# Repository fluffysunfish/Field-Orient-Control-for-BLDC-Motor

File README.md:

# Field-Orient-Control-for-BLDC-Motor

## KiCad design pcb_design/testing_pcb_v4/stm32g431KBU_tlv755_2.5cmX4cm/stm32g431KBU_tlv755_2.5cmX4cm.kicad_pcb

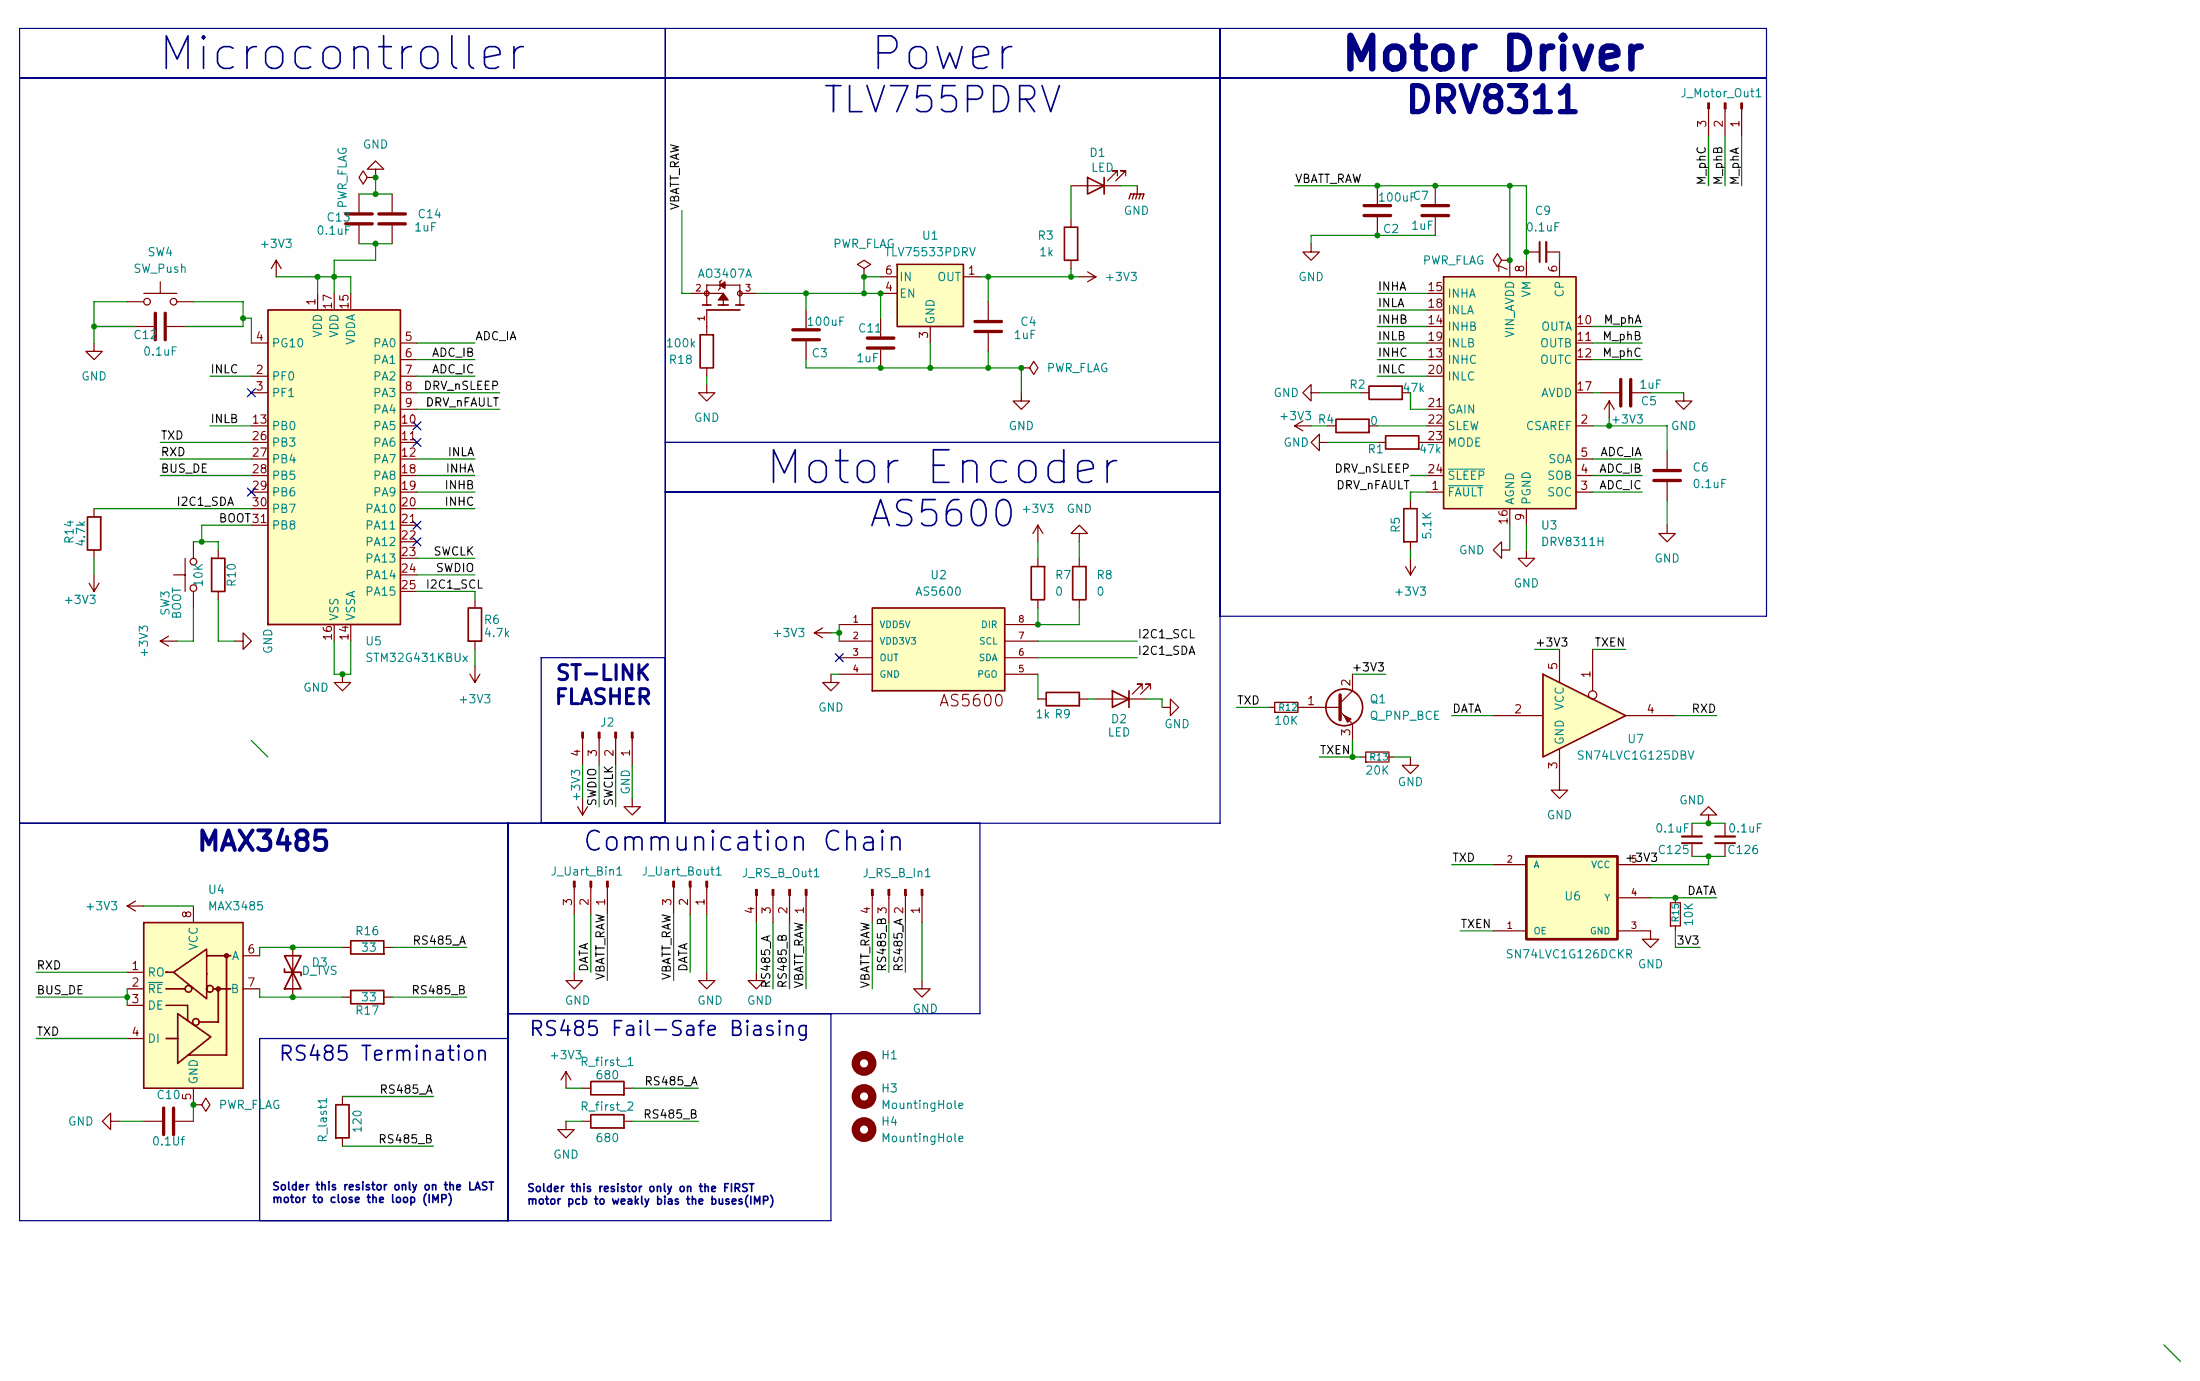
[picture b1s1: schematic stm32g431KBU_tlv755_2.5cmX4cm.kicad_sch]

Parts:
C2, C3: 100uF; C_0805_2012Metric
C4: 1uF; C_0805_2012Metric
C5: 1uF; C_0402_1005Metric
C6: 0.1uF; C_0402_1005Metric
C7, C11, C14: 1uF; C_0603_1608Metric
C9, C12, C13: 0.1uF; C_0603_1608Metric
C10: 0.1Uf; C_0402_1005Metric
C125, C126: 0.1uF; C_0603_1608Metric_Pad1.08x0.95mm_HandSolder
D1, D2: LED; LED_0603_1608Metric
D3: D_TVS; TSOT-23
H1, H3, H4: MountingHole; MountingHole_2.2mm_M2
J2: ST-LINK Flasher; PinHeader_1x04_P2.54mm_Vertical
J_Motor_Out1: Conn_01x03_Pin; PinHeader_1x03_P2.54mm_Vertical
J_RS_B_In1: Conn_01x04_Pin; JST_PH_S4B-PH-K_1x04_P2.00mm_Horizontal
J_RS_B_Out1: Conn_01x04_Pin; JST_PH_S4B-PH-K_1x04_P2.00mm_Horizontal
J_Uart_Bin1: Conn_01x03_Pin; JST_PH_S3B-PH-K_1x03_P2.00mm_Horizontal
J_Uart_Bout1: Conn_01x03_Pin; JST_PH_S3B-PH-K_1x03_P2.00mm_Horizontal
Q1: Q_PNP_BCE; SOT-23-3
Q2: AO3407A; SOT95P280X125-3N; PARTREV 5
R1, R2: 47k; R_0402_1005Metric
R3, R9: 1k; R_0402_1005Metric
R4: 0; R_0402_1005Metric
R5: 5.1K; R_0402_1005Metric
R6: 4.7k; R_0402_1005Metric
R7, R8: 0; R_0805_2012Metric
R10: 10K; R_0402_1005Metric
R12, R15: 10K; R_0603_1608Metric_Pad0.98x0.95mm_HandSolder
R13: 20K; R_0603_1608Metric_Pad0.98x0.95mm_HandSolder
R14: 4.7k; R_0805_2012Metric_Pad1.20x1.40mm_HandSolder
R16, R17: 33; R_0805_2012Metric
R18: 100k; R_0805_2012Metric
R_first_1, R_first_2: 680; R_0805_2012Metric_Pad1.20x1.40mm_HandSolder
R_last1: 120; R_0805_2012Metric_Pad1.20x1.40mm_HandSolder
SW3: BOOT; SW_Push_SPST_NO_Alps_SKRK
SW4: SW_Push; SW_Push_SPST_NO_Alps_SKRK
U1: TLV75533PDRV; WSON-6-1EP_2x2mm_P0.65mm_EP1x1.6mm
U2: AS5600; SOIC8
U3: DRV8311H; Texas_RRW0024A_WQFN-24-1EP_3x3mm_P0.4mm_EP1.9x1.9mm
U4: MAX3485; SOIC-8_3.9x4.9mm_P1.27mm
U5: STM32G431KBUx; QFN-32-1EP_5x5mm_P0.5mm_EP3.45x3.45mm
U6: SN74LVC1G126DCKR; SOT-353_SC-70-5
U7: SN74LVC1G125DBV; SOT-353_SC-70-5

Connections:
/ADC_IA: U3.5 (SOA), U5.5 (PA0)
/ADC_IB: U3.4 (SOB), U5.6 (PA1)
/ADC_IC: U3.3 (SOC), U5.7 (PA2)
/BOOT: R10.2, SW3.2, U5.31 (PB8)
/BUS_DE: U4.2 (~RE), U4.3 (DE), U5.28 (PB5)
/DATA: J_Uart_Bin1.2, J_Uart_Bout1.2, R15.2, U6.4 (Y), U7.2
/DRV_nFAULT: R5.1, U3.1 (~FAULT), U5.9 (PA4)
/DRV_nSLEEP: U3.24 (~SLEEP), U5.8 (PA3)
/I2C1_SCL: R6.1, U2.7 (SCL), U5.25 (PA15)
/I2C1_SDA: R14.2, U2.6 (SDA), U5.30 (PB7)
/INHA: U3.15 (INHA), U5.18 (PA8)
/INHB: U3.14 (INHB), U5.19 (PA9)
/INHC: U3.13 (INHC), U5.20 (PA10)
/INLA: U3.18 (INLA), U5.12 (PA7)
/INLB: U3.19 (INLB), U5.13 (PB0)
/INLC: U3.20 (INLC), U5.2 (PF0)
/M_phA: J_Motor_Out1.1, U3.10 (OUTA)
/M_phB: J_Motor_Out1.2, U3.11 (OUTB)
/M_phC: J_Motor_Out1.3, U3.12 (OUTC)
/RS485_A: J_RS_B_In1.2, J_RS_B_Out1.3, R16.2, R_first_1.2, R_last1.1; also elsewhere on the board
/RS485_B: J_RS_B_In1.3, J_RS_B_Out1.2, R17.2, R_first_2.2, R_last1.2; also elsewhere on the board
/RXD: U4.1 (RO), U5.27 (PB4), U7.4
/SWCLK: J2.2, U5.23 (PA13)
/SWDIO: J2.3, U5.24 (PA14)
/TXD: R12.1, U4.4 (DI), U5.26 (PB3), U6.2 (A)
/TXEN: Q1.3 (E), R13.1, U6.1 (OE), U7.1
/VBATT_RAW: C2.1, C7.1, C9.1, J_RS_B_In1.4, J_RS_B_Out1.1, J_Uart_Bin1.1, J_Uart_Bout1.3, Q2.2, U3.7 (VIN_AVDD), U3.8 (VM)
GND: C2.2, C3.2, C4.2, C5.2, C6.2, C7.2, C10.2, C11.2, C12.2, C13.2, C14.1, C125.2, C126.2, D1.1 (K), D2.1 (K), J2.1, J_RS_B_In1.1, J_RS_B_Out1.4, J_Uart_Bin1.3, J_Uart_Bout1.1, R1.1, R2.1, R8.2, R10.1, R13.2, R18.1, R_first_2.1, SW4.1, U1.3 (GND), U1.7 (GND), U2.4 (GND), U3.9 (PGND), U3.16 (AGND), U3.25 (PGND), U5.14 (VSSA), U5.16 (VSS), U5.32 (VSS), U5.33 (VSS), U6.3 (GND), U7.3 (GND); also elsewhere on the board
unnamed: D1.2 (A), R3.1
unnamed: D2.2 (A), R9.2
unnamed: D3.1 (A1), R17.1, U4.7 (B)
unnamed: D3.2 (A2), R16.1, U4.6 (A)
unnamed: Q1.1 (B), R12.2
unnamed: Q2.1, R18.2
unnamed: C3.1, C11.1, Q2.3, U1.4 (EN), U1.6 (IN)
unnamed: R7.1, R8.1, U2.8 (DIR)
unnamed: R9.1, U2.5 (PGO)
unnamed: C5.1, U3.17 (AVDD)
unnamed: C9.2, U3.6 (CP)
unnamed: R2.2, U3.21 (GAIN)
unnamed: R1.2, U3.23 (MODE)
unnamed: R4.2, U3.22 (SLEW)
unnamed: C10.1, U4.5 (GND)
unnamed: C12.1, SW4.2, U5.4 (PG10)

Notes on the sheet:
Solder this resistor only on the LAST motor to close the loop (IMP)
Solder this resistor only on the FIRST motor pcb to weakly bias the buses(IMP)
Motor Encoder
AS5600
Power
Motor Driver
Microcontroller
TLV755PDRV
ST-LINK FLASHER
Communication Chain
DRV8311
MAX3485
RS485 Termination
RS485 Fail-Safe Biasing

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
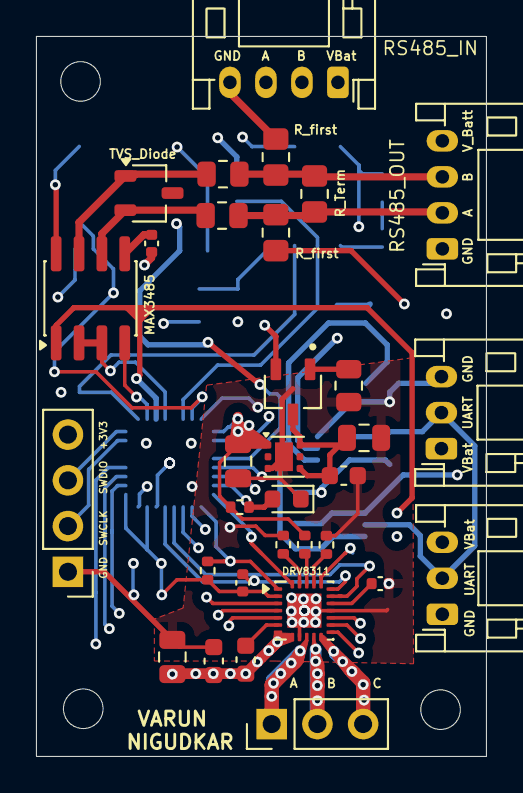
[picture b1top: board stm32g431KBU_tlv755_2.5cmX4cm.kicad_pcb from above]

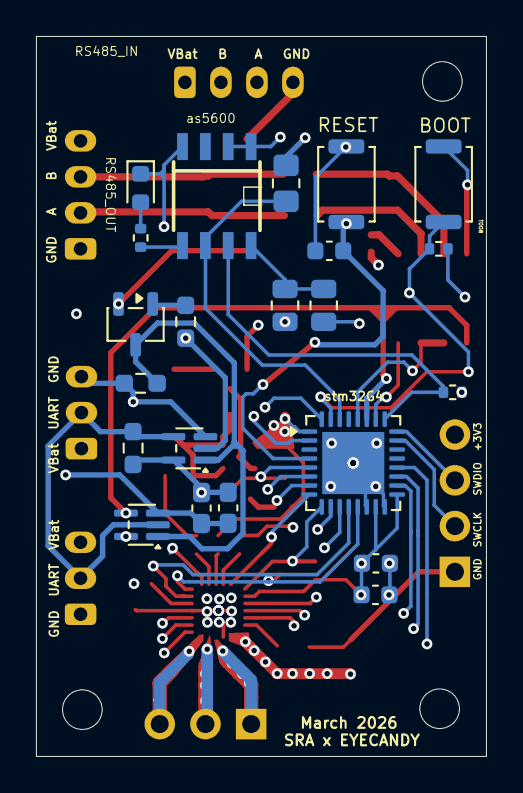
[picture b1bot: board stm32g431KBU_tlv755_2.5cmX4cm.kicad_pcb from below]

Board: 4 copper layers, 25.0 x 40.0 mm, 57 parts (22 on the bottom side), 45 nets.

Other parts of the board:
R14(DNI)1: 120; R_0805_2012Metric_Pad1.20x1.40mm_HandSolder
R14(DNI)2, R15(DNI)1: 680; R_0805_2012Metric_Pad1.20x1.40mm_HandSolder

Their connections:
/RS485_A: R14(DNI)1.1, R14(DNI)2.2; also elsewhere on the board
/RS485_B: R14(DNI)1.2, R15(DNI)1.2; also elsewhere on the board
GND: R15(DNI)1.1; also elsewhere on the board

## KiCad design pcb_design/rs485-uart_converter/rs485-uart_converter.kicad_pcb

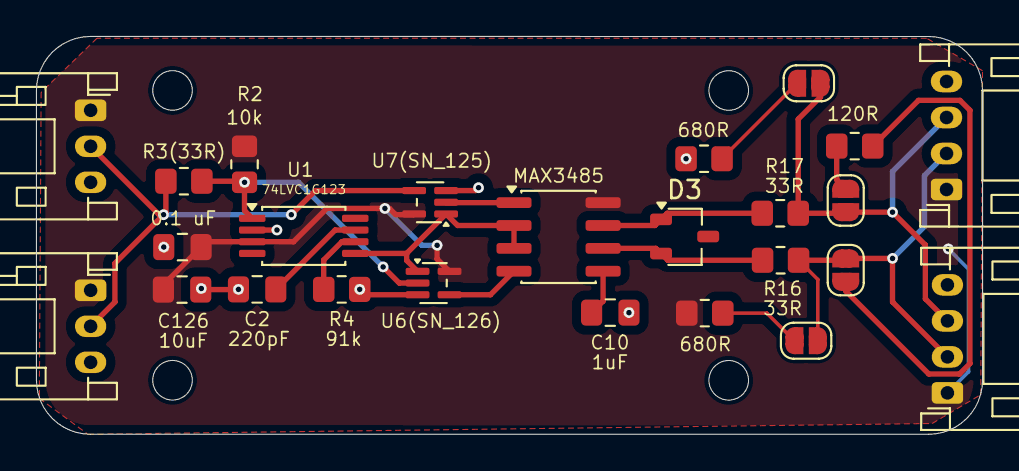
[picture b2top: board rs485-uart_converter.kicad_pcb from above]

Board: 2 copper layers, 52.6 x 22.1 mm, 29 parts (0 on the bottom side), 18 nets.

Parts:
0.1 uF: 0.1uF; C_0805_2012Metric_Pad1.18x1.45mm_HandSolder
33R: 33; R_0805_2012Metric_Pad1.20x1.40mm_HandSolder
120R: 120; R_0805_2012Metric_Pad1.20x1.40mm_HandSolder
680R, 680R#2: 680; R_0805_2012Metric_Pad1.20x1.40mm_HandSolder
C2: 220 pF; C_0805_2012Metric_Pad1.18x1.45mm_HandSolder
C10: 1uf; C_0805_2012Metric_Pad1.18x1.45mm_HandSolder
C126: 1uF; C_0805_2012Metric_Pad1.18x1.45mm_HandSolder
D3: D_TVS; TSOT-23
GND  B  A  3V3: Conn_01x04_Pin; JST_PH_S4B-PH-K_1x04_P2.00mm_Horizontal
H1, H2, H3, H4: MountingHole; MountingHole_2.2mm_M2
JP1, JP2, JP3, JP4: SolderJumper_2_Open; SolderJumper-2_P1.3mm_Open_RoundedPad1.0x1.5mm
JST-UART1, JST-UART2: Conn_01x03_Pin; JST_PH_S3B-PH-K_1x03_P2.00mm_Horizontal
JST_RS485: Conn_01x04_Pin; JST_PH_S4B-PH-K_1x04_P2.00mm_Horizontal
MAX3485: MAX3485; SOIC-8_3.9x4.9mm_P1.27mm
R2: 10k; R_0805_2012Metric_Pad1.20x1.40mm_HandSolder
R3(33R), R16: 33; R_0805_2012Metric_Pad1.20x1.40mm_HandSolder
R4: 91k; R_0805_2012Metric_Pad1.20x1.40mm_HandSolder
U1: 74LVC1G123; TSSOP-8_4.4x3mm_P0.65mm
U6(SN_126): SN74LVC1G126DCKR; SOT-353_SC-70-5
U7(SN_125): SN74LVC1G125DBV; SOT-353_SC-70-5

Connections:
3V3: 0.1 uF.1, 680R#2.1, C126.1, GND B A 3V3.1, JST-UART1.1, JST-UART2.1, JST_RS485.1, MAX3485.8 (VCC), R2.1, U1.3 (~CLR), U6(SN_126).5 (VCC), U7(SN_125).5 (VCC)
/DATA: R2.2, R3(33R).2, U1.1 (~A), U6(SN_126).2 (A)
/DATA_RAW: JST-UART1.2, JST-UART2.2, R3(33R).1, U7(SN_125).4
/DI: MAX3485.4 (DI), U6(SN_126).4 (Y)
/RO: MAX3485.1 (RO), U7(SN_125).2
/RS485_A: GND B A 3V3.2, JP1.2 (B), JP4.1 (A), JST_RS485.2, R16.2
/RS485_B: 33R.2, GND B A 3V3.3, JP2.1 (A), JP3.1 (A), JST_RS485.3
/TXEN: MAX3485.2 (~RE), MAX3485.3 (DE), U1.5 (Q), U6(SN_126).1 (OE), U7(SN_125).1
GND: 0.1 uF.2, 680R.1, C2.2, C10.2, C126.2, GND B A 3V3.4, JST-UART1.3, JST-UART2.3, JST_RS485.4, R4.1, U1.2 (B), U6(SN_126).3 (GND), U7(SN_125).3 (GND)
unnamed: 33R.1, D3.1 (A1), MAX3485.7 (B)
unnamed: D3.2 (A2), MAX3485.6 (A), R16.1
unnamed: 680R#2.2, JP1.1 (A)
unnamed: 680R.2, JP2.2 (B)
unnamed: 120R.2, JP3.2 (B)
unnamed: 120R.1, JP4.2 (B)
unnamed: R4.2, U1.6 (Cext)
unnamed: C2.1, U1.7 (RCext)
unnamed: C10.1, MAX3485.5 (GND)

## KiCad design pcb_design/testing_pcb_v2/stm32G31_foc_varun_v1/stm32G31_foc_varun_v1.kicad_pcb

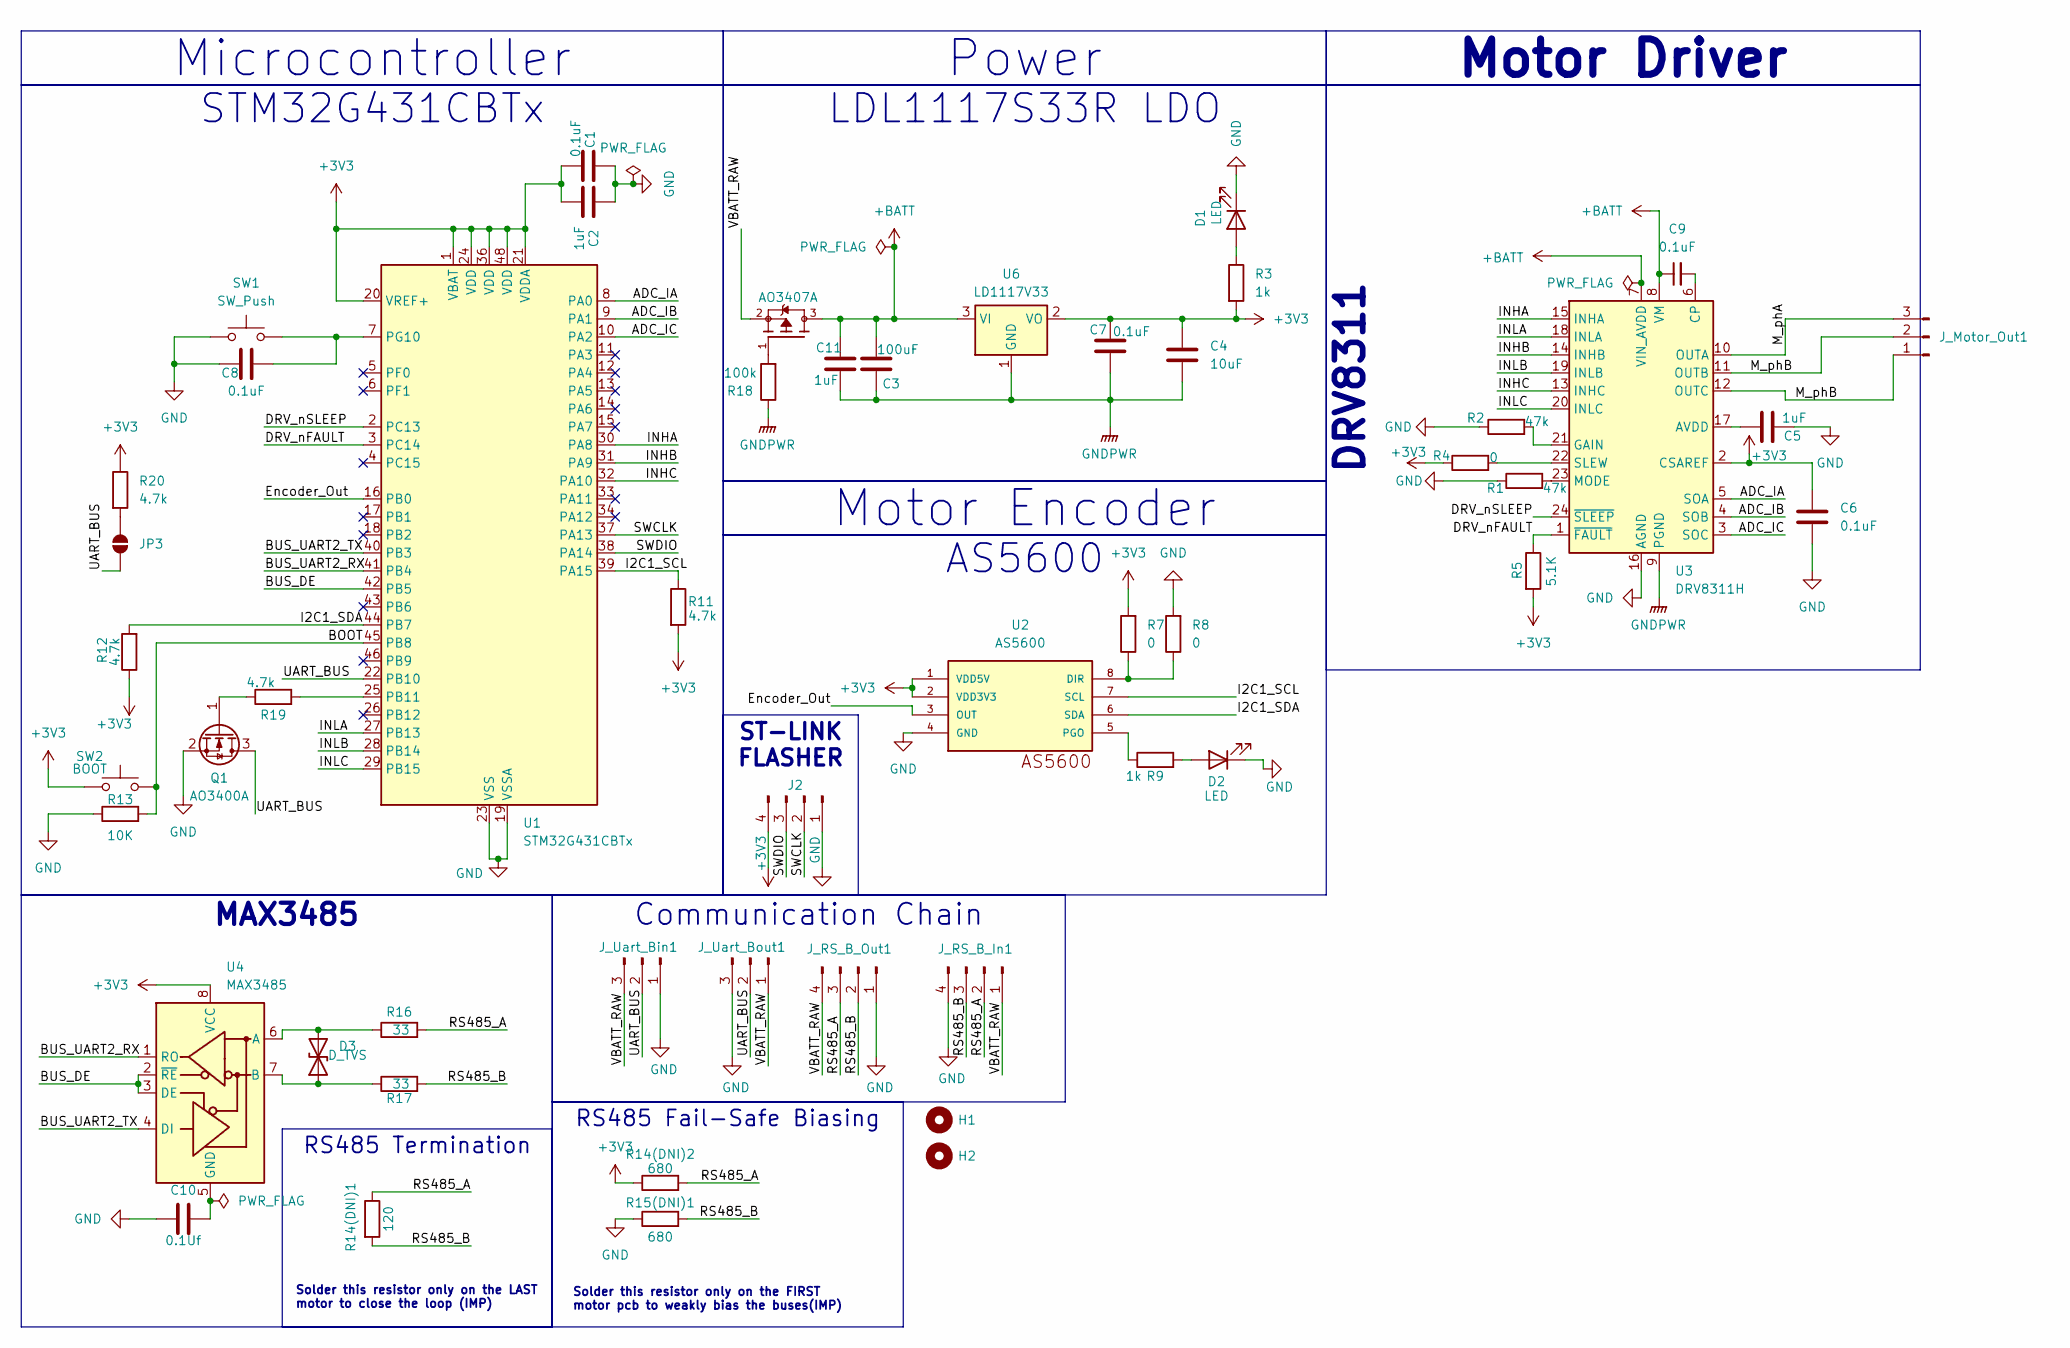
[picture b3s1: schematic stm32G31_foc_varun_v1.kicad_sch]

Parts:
C1, C6, C7, C8, C9: 0.1uF; C_0603_1608Metric_Pad1.08x0.95mm_HandSolder
C2, C5: 1uF; C_0603_1608Metric_Pad1.08x0.95mm_HandSolder
C3: 100uF; C_0805_2012Metric_Pad1.18x1.45mm_HandSolder
C4: 10uF; C_1206_3216Metric
C10: 0.1Uf; C_0603_1608Metric_Pad1.08x0.95mm_HandSolder
C11: 1uF; C_0805_2012Metric
D1, D2: LED; LED_0603_1608Metric_Pad1.05x0.95mm_HandSolder
D3: D_TVS; TSOT-23
H1, H2: MountingHole; MountingHole_2.2mm_M2
J2: ST-LINK Flasher; PinSocket_1x04_P2.54mm_Vertical
JP3: SolderJumper_2_Open; SolderJumper-2_P1.3mm_Open_RoundedPad1.0x1.5mm
J_Motor_Out1: Conn_01x03_Pin; JST_PH_S3B-PH-K_1x03_P2.00mm_Horizontal
J_RS_B_In1: Conn_01x04_Pin; JST_PH_S4B-PH-K_1x04_P2.00mm_Horizontal
J_RS_B_Out1: Conn_01x04_Pin; JST_PH_S4B-PH-K_1x04_P2.00mm_Horizontal
J_Uart_Bin1: Conn_01x03_Pin; JST_PH_S3B-PH-K_1x03_P2.00mm_Horizontal
J_Uart_Bout1: Conn_01x03_Pin; JST_PH_S3B-PH-K_1x03_P2.00mm_Horizontal
Q1: AO3400A; SOT-23
Q2: AO3407A; SOT95P280X125-3N; PARTREV 5
R1, R2: 47k; R_0603_1608Metric_Pad0.98x0.95mm_HandSolder
R3, R9: 1k; R_0603_1608Metric_Pad0.98x0.95mm_HandSolder
R4, R7, R8: 0; R_0603_1608Metric_Pad0.98x0.95mm_HandSolder
R5: 5.1K; R_0603_1608Metric_Pad0.98x0.95mm_HandSolder
R11, R12, R19, R20: 4.7k; R_0603_1608Metric_Pad0.98x0.95mm_HandSolder
R13: 10K; R_0603_1608Metric_Pad0.98x0.95mm_HandSolder
R14(DNI)1: 120; C_0805_2012Metric
R14(DNI)2, R15(DNI)1: 680; R_0603_1608Metric_Pad0.98x0.95mm_HandSolder
R16, R17: 33; R_0603_1608Metric_Pad0.98x0.95mm_HandSolder
R18: 100k; R_0603_1608Metric_Pad0.98x0.95mm_HandSolder
SW1: SW_Push; SW_Push_SPST_NO_Alps_SKRK
SW2: BOOT; SW_Push_SPST_NO_Alps_SKRK
U1: STM32G431CBTx; LQFP-48_7x7mm_P0.5mm
U2: AS5600; SOIC8
U3: DRV8311H; Texas_RRW0024A_WQFN-24-1EP_3x3mm_P0.4mm_EP1.9x1.9mm
U4: MAX3485; SOIC-8_3.9x4.9mm_P1.27mm
U6: LD1117V33; TO-252-2

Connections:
+3V3: C1.1, C2.2, C4.1, C6.1, C7.1, J2.4, R3.2, R4.1, R5.2, R7.2, R11.2, R12.1, R14(DNI)2.1, R20.1, SW2.1, U1.1 (VBAT), U1.20 (VREF+), U1.21 (VDDA), U1.24 (VDD), U1.36 (VDD), U1.48 (VDD), U2.1 (VDD5V), U2.2 (VDD3V3), U3.2 (CSAREF), U4.8 (VCC), U6.2 (VO)
+BATT: C3.1, C9.1, C11.1, Q2.3, U3.7 (VIN_AVDD), U3.8 (VM), U6.3 (VI)
/ADC_IA: U1.8 (PA0), U3.5 (SOA)
/ADC_IB: U1.9 (PA1), U3.4 (SOB)
/ADC_IC: U1.10 (PA2), U3.3 (SOC)
/BOOT: R13.2, SW2.2, U1.45 (PB8)
/BUS_DE: U1.42 (PB5), U4.2 (~RE), U4.3 (DE)
/BUS_UART2_RX: U1.41 (PB4), U4.1 (RO)
/BUS_UART2_TX: U1.40 (PB3), U4.4 (DI)
/DRV_nFAULT: R5.1, U1.3 (PC14), U3.1 (~FAULT)
/DRV_nSLEEP: U1.2 (PC13), U3.24 (~SLEEP)
/Encoder_Out: U1.16 (PB0), U2.3 (OUT)
/I2C1_SCL: R11.1, U1.39 (PA15), U2.7 (SCL)
/I2C1_SDA: R12.2, U1.44 (PB7), U2.6 (SDA)
/INHA: U1.30 (PA8), U3.15 (INHA)
/INHB: U1.31 (PA9), U3.14 (INHB)
/INHC: U1.32 (PA10), U3.13 (INHC)
/INLA: U1.27 (PB13), U3.18 (INLA)
/INLB: U1.28 (PB14), U3.19 (INLB)
/INLC: U1.29 (PB15), U3.20 (INLC)
/M_phA: J_Motor_Out1.3, U3.10 (OUTA)
/M_phB: J_Motor_Out1.1, J_Motor_Out1.2, U3.11 (OUTB), U3.12 (OUTC)
/RS485_A: J_RS_B_In1.2, J_RS_B_Out1.3, R14(DNI)1.1, R14(DNI)2.2, R16.2
/RS485_B: J_RS_B_In1.3, J_RS_B_Out1.2, R14(DNI)1.2, R15(DNI)1.2, R17.2
/SWCLK: J2.2, U1.37 (PA13)
/SWDIO: J2.3, U1.38 (PA14)
/UART_BUS: JP3.1 (A), J_Uart_Bin1.2, J_Uart_Bout1.2, Q1.3 (D), U1.22 (PB10)
/VBATT_RAW: J_RS_B_In1.1, J_RS_B_Out1.4, J_Uart_Bin1.3, J_Uart_Bout1.1, Q2.2
GND: C1.2, C2.1, C5.2, C6.2, C8.2, C10.2, D1.1 (K), D2.1 (K), J2.1, J_RS_B_In1.4, J_RS_B_Out1.1, J_Uart_Bin1.1, J_Uart_Bout1.3, Q1.2 (S), R1.1, R2.1, R8.2, R13.1, R15(DNI)1.1, SW1.1, U1.19 (VSSA), U1.23 (VSS), U1.35 (VSS), U1.47 (VSS), U2.4 (GND), U3.16 (AGND)
GNDPWR: C3.2, C4.2, C7.2, C11.2, R18.1, U3.9 (PGND), U3.25 (PGND), U6.1 (GND)
unnamed: D1.2 (A), R3.1
unnamed: D2.2 (A), R9.2
unnamed: D3.1 (A1), R17.1, U4.7 (B)
unnamed: D3.2 (A2), R16.1, U4.6 (A)
unnamed: JP3.2 (B), R20.2
unnamed: Q1.1 (G), R19.1
unnamed: Q2.1, R18.2
unnamed: R19.2, U1.25 (PB11)
unnamed: C8.1, SW1.2, U1.7 (PG10)
unnamed: R7.1, R8.1, U2.8 (DIR)
unnamed: R9.1, U2.5 (PGO)
unnamed: C5.1, U3.17 (AVDD)
unnamed: C9.2, U3.6 (CP)
unnamed: R2.2, U3.21 (GAIN)
unnamed: R1.2, U3.23 (MODE)
unnamed: R4.2, U3.22 (SLEW)
unnamed: C10.1, U4.5 (GND)

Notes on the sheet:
Solder this resistor only on the FIRST motor pcb to weakly bias the buses(IMP)
Solder this resistor only on the LAST motor to close the loop (IMP)
Microcontroller
ST-LINK FLASHER
Motor Driver
RS485 Termination
Power
Motor Encoder
MAX3485
DRV8311
STM32G431CBTx
AS5600
LDL1117S33R LDO
Communication Chain
RS485 Fail-Safe Biasing

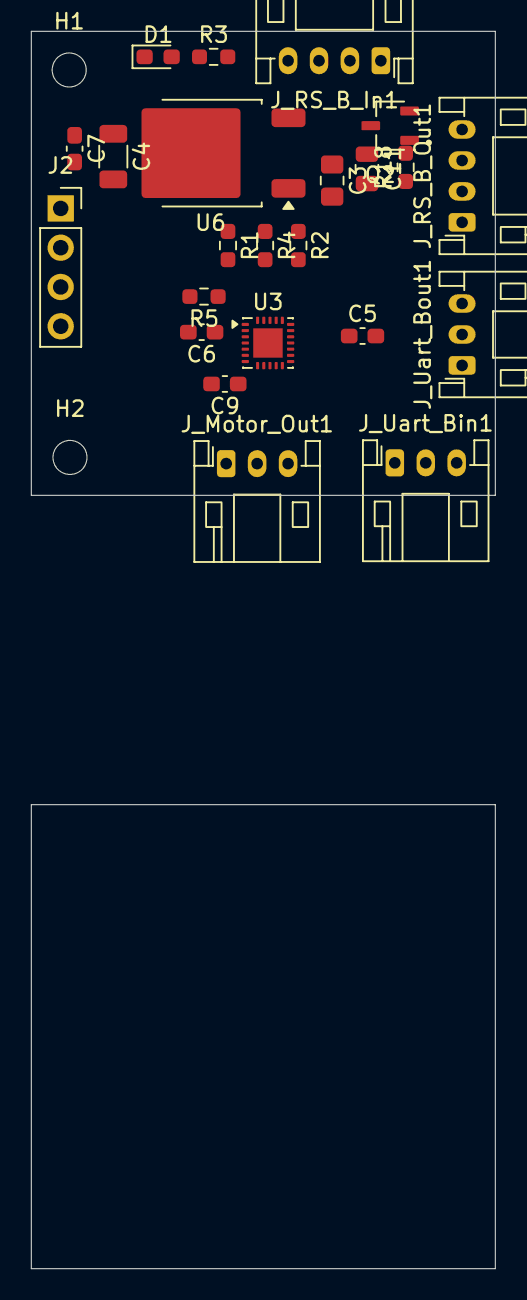
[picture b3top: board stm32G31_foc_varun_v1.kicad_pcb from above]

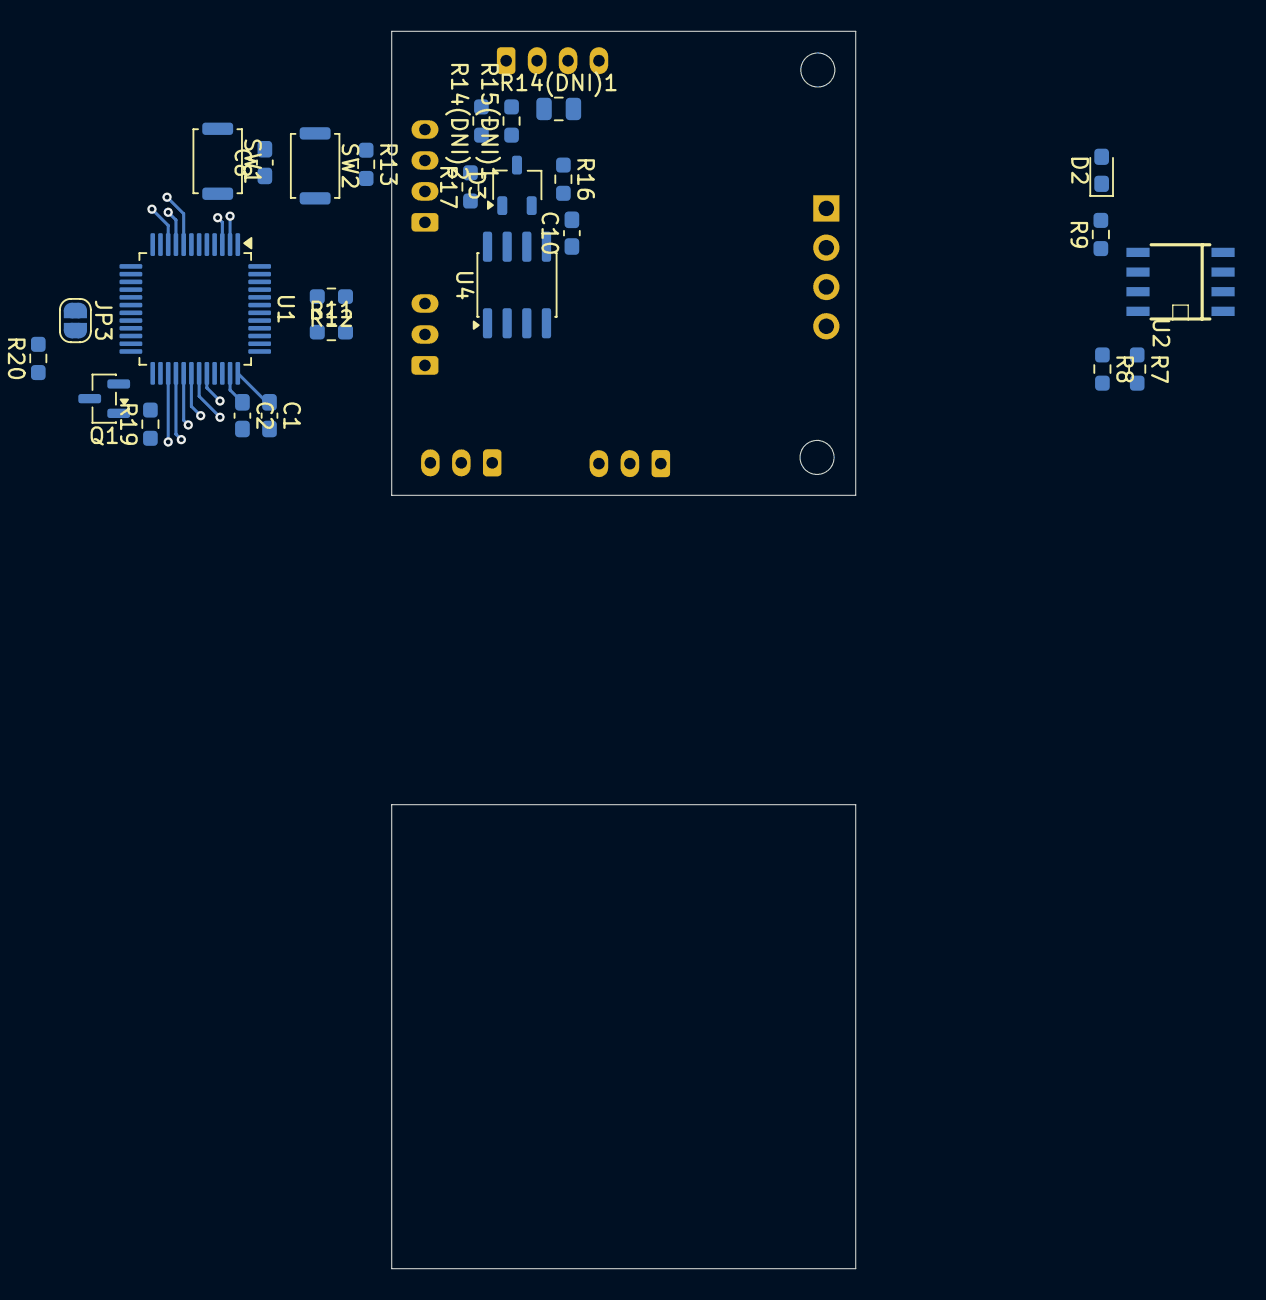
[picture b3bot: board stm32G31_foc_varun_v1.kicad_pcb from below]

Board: 4 copper layers, 51 parts (26 on the bottom side), 47 nets.

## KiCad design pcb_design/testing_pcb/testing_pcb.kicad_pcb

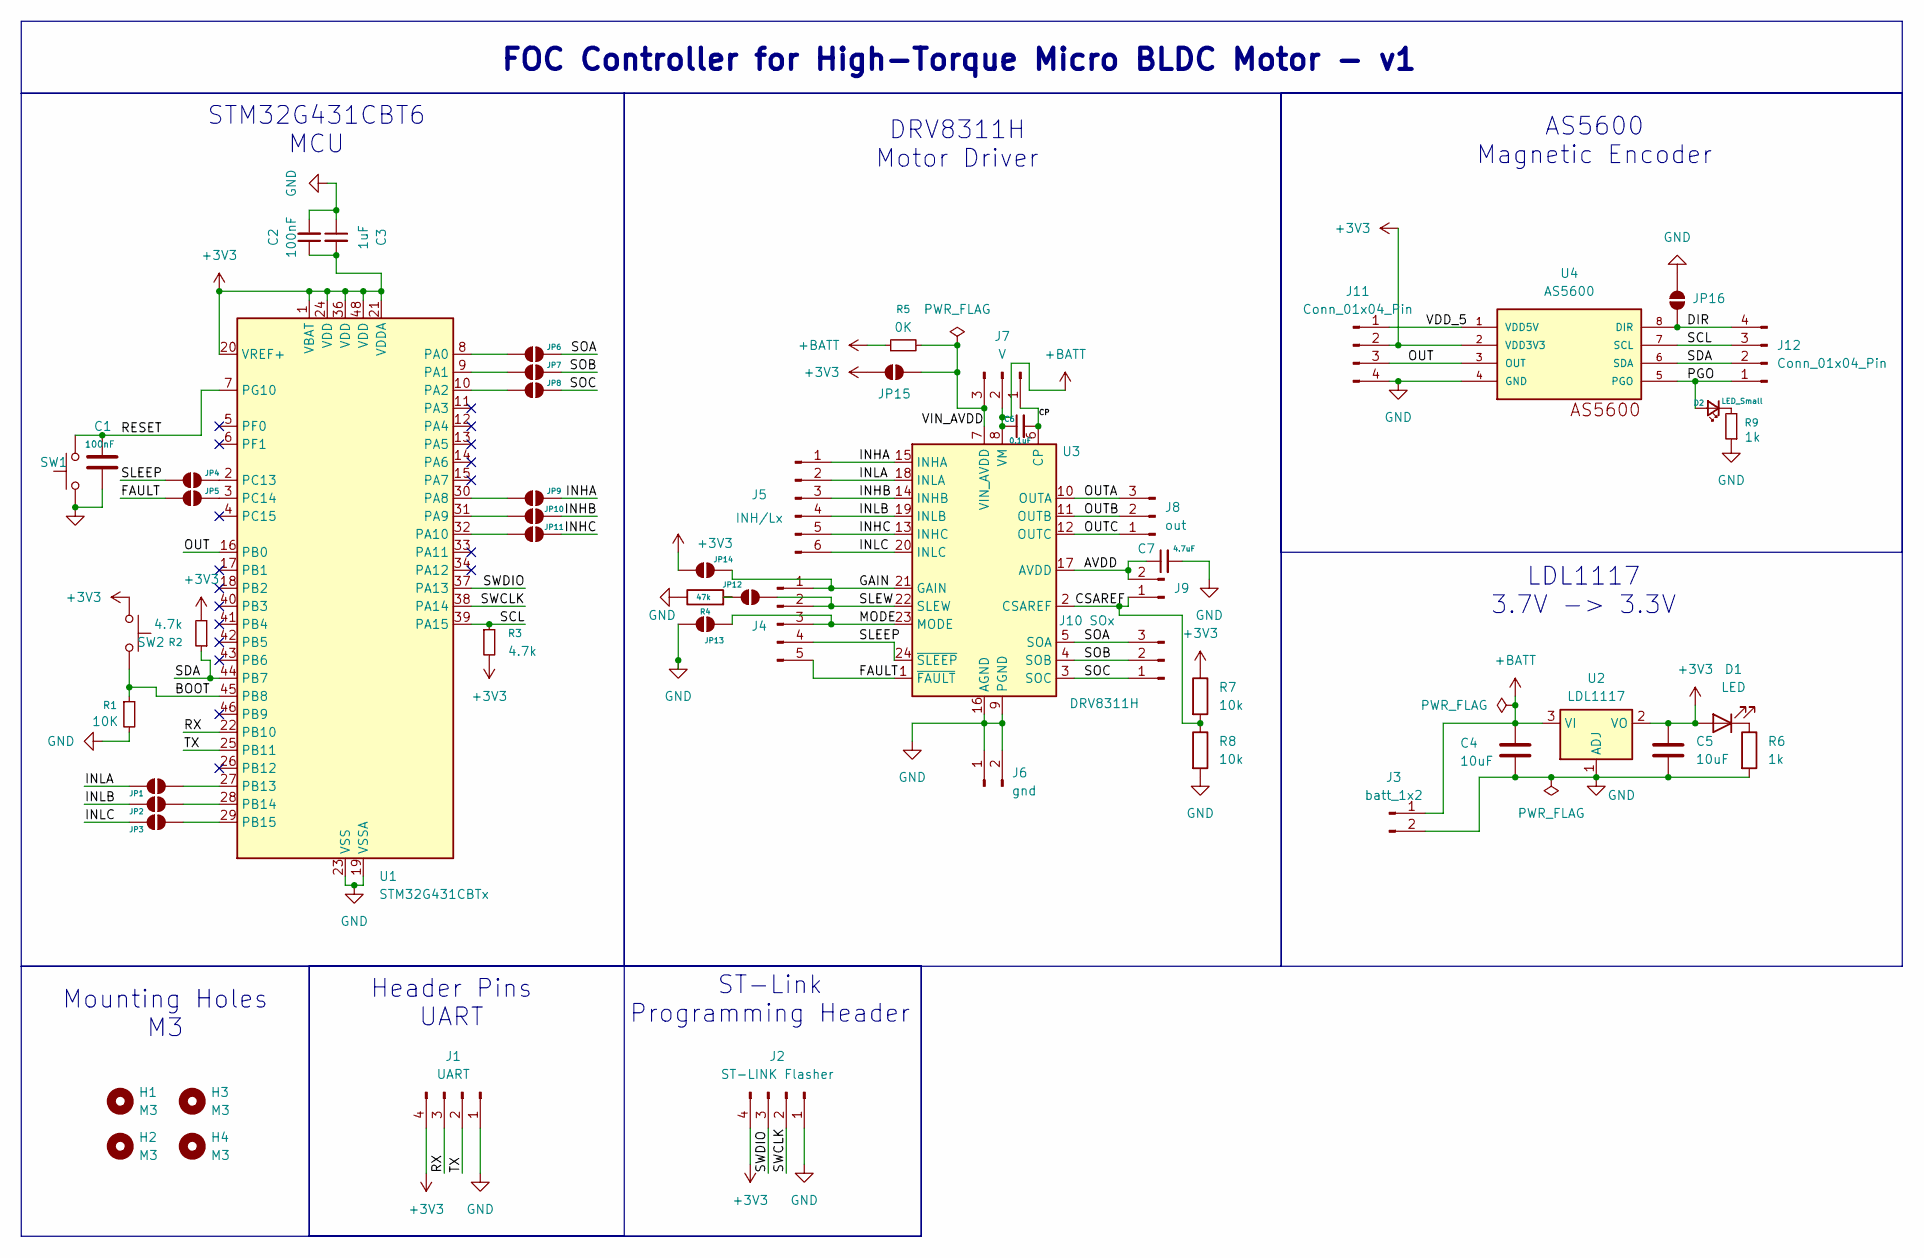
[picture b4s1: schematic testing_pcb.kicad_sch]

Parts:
C1: 100nF; C_0805_2012Metric_Pad1.18x1.45mm_HandSolder
C2: 100nF; C_0805_2012Metric
C3: 1uF; C_0805_2012Metric
C4, C5: 10uF; C_0805_2012Metric
C6: 0.1uF; C_0805_2012Metric
C7: 4.7uF; C_0805_2012Metric
D1: LED; LED_0805_2012Metric
D2: LED_Small; LED_0805_2012Metric
H1, H2, H3, H4: M3; MountingHole_3mm
J1: UART; PinSocket_1x04_P2.54mm_Vertical
J2: ST-LINK Flasher; PinSocket_1x04_P2.54mm_Vertical
J3: batt_1x2; PinSocket_1x02_P2.54mm_Vertical
J4: PinSocket_1x05_P2.54mm_Vertical
J5: INH/Lx; PinSocket_1x06_P2.54mm_Vertical
J6: gnd; PinSocket_1x02_P2.54mm_Vertical
J7: V; PinSocket_1x03_P2.54mm_Vertical
J8: out; PinSocket_1x03_P2.54mm_Vertical
J9: PinSocket_1x02_P2.54mm_Vertical
J10: SOx; PinSocket_1x03_P2.54mm_Vertical
J11, J12: Conn_01x04_Pin; PinSocket_1x04_P2.54mm_Vertical
JP1, JP2, JP3, JP4, JP5, JP6, JP7, JP8, JP9, JP10, JP11, JP12, JP13, JP14, JP15, JP16: SolderJumper_2_Open; SolderJumper-2_P1.3mm_Open_RoundedPad1.0x1.5mm
R1: 10K; R_0805_2012Metric
R2, R3: 4.7k; R_0805_2012Metric
R4: 47k; R_0805_2012Metric
R5: 0K; R_0805_2012Metric
R6: 1k; R_0805_2012Metric
R7, R8: 10k; R_0805_2012Metric
R9: 1k; LED_0805_2012Metric
SW1, SW2: SW_Push; SW_PUSH_6mm_H5mm
U1: STM32G431CBTx; LQFP-48_7x7mm_P0.5mm
U2: LDL1117; SOT-223-3_TabPin2
U3: DRV8311H; Texas_RRW0024A_WQFN-24-1EP_3x3mm_P0.4mm_EP1.9x1.9mm
U4: AS5600; SOIC8

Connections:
+3V3: C2.1, C3.2, C5.1, D1.2 (A), J1.4, J2.4, J11.2, JP14.1 (A), JP15.1 (A), R2.2, R3.2, R7.1, SW2.1, U1.1 (VBAT), U1.20 (VREF+), U1.21 (VDDA), U1.24 (VDD), U1.36 (VDD), U1.48 (VDD), U2.2 (VO), U4.2 (VDD3V3); also elsewhere on the board
+BATT: C4.1, C6.1, J3.1, J7.2, R5.1, U2.3 (VI), U3.8 (VM)
/AVDD: C7.1, J9.2, U3.17 (AVDD)
/BOOT: R1.1, SW2.2, U1.45 (PB8); also elsewhere on the board
/CP: C6.2, J7.1, U3.6 (CP)
/CSAREF: J9.1, R7.2, R8.1, U3.2 (CSAREF)
/DIR: J12.4, JP16.1 (A), U4.8 (DIR)
/FAULT: J4.5, JP5.1 (A), U3.1 (~FAULT)
/GAIN: J4.1, JP14.2 (B), U3.21 (GAIN)
/INHA: J5.1, JP9.2 (B), U3.15 (INHA)
/INHB: J5.3, JP10.2 (B), U3.14 (INHB)
/INHC: J5.5, JP11.2 (B), U3.13 (INHC)
/INLA: J5.2, JP1.2 (B), U3.18 (INLA)
/INLB: J5.4, JP2.2 (B), U3.19 (INLB)
/INLC: J5.6, JP3.2 (B), U3.20 (INLC)
/MODE: J4.3, JP13.2 (B), U3.23 (MODE)
/OUT: J11.3, U1.16 (PB0), U4.3 (OUT)
/OUTA: J8.3, U3.10 (OUTA)
/OUTB: J8.2, U3.11 (OUTB)
/OUTC: J8.1, U3.12 (OUTC)
/PGO: D2.2 (A), J12.1, U4.5 (PGO)
/RESET: C1.1, SW1.2, U1.7 (PG10); also elsewhere on the board
/RX: J1.3, U1.22 (PB10); also elsewhere on the board
/SCL: J12.3, R3.1, U1.39 (PA15), U4.7 (SCL)
/SDA: J12.2, R2.1, U1.44 (PB7), U4.6 (SDA)
/SLEEP: J4.4, JP4.1 (A), U3.24 (~SLEEP)
/SLEW: J4.2, JP12.2 (B), U3.22 (SLEW)
/SOA: J10.3, JP6.2 (B), U3.5 (SOA)
/SOB: J10.2, JP7.2 (B), U3.4 (SOB)
/SOC: J10.1, JP8.2 (B), U3.3 (SOC)
/SWCLK: J2.2, U1.38 (PA14)
/SWDIO: J2.3, U1.37 (PA13)
/TX: J1.2, U1.25 (PB11); also elsewhere on the board
/VDD_5: J11.1, U4.1 (VDD5V)
/VIN_AVDD: J7.3, JP15.2 (B), R5.2, U3.7 (VIN_AVDD)
GND: C1.2, C2.2, C3.1, C4.2, C5.2, C7.2, J1.1, J2.1, J3.2, J6.1, J6.2, J11.4, JP13.1 (A), JP16.2 (B), R1.2, R4.1, R6.2, R8.2, R9.1, SW1.1, U1.19 (VSSA), U1.23 (VSS), U1.35 (VSS), U1.47 (VSS), U2.1 (ADJ), U3.9 (PGND), U3.16 (AGND), U3.25 (PGND), U4.4 (GND); also elsewhere on the board
unnamed: D1.1 (K), R6.1
unnamed: D2.1 (K), R9.2
unnamed: JP1.1 (A), U1.27 (PB13)
unnamed: JP2.1 (A), U1.28 (PB14)
unnamed: JP3.1 (A), U1.29 (PB15)
unnamed: JP4.2 (B), U1.2 (PC13)
unnamed: JP5.2 (B), U1.3 (PC14)
unnamed: JP6.1 (A), U1.8 (PA0)
unnamed: JP7.1 (A), U1.9 (PA1)
unnamed: JP8.1 (A), U1.10 (PA2)
unnamed: JP9.1 (A), U1.30 (PA8)
unnamed: JP10.1 (A), U1.31 (PA9)
unnamed: JP11.1 (A), U1.32 (PA10)
unnamed: JP12.1 (A), R4.2

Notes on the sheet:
DRV8311H Motor Driver
Mounting Holes M3
LDL1117 3.7V -> 3.3V
FOC Controller for High-Torque Micro BLDC Motor - v1
AS5600 Magnetic Encoder
Header Pins UART
ST-Link Programming Header
STM32G431CBT6 MCU

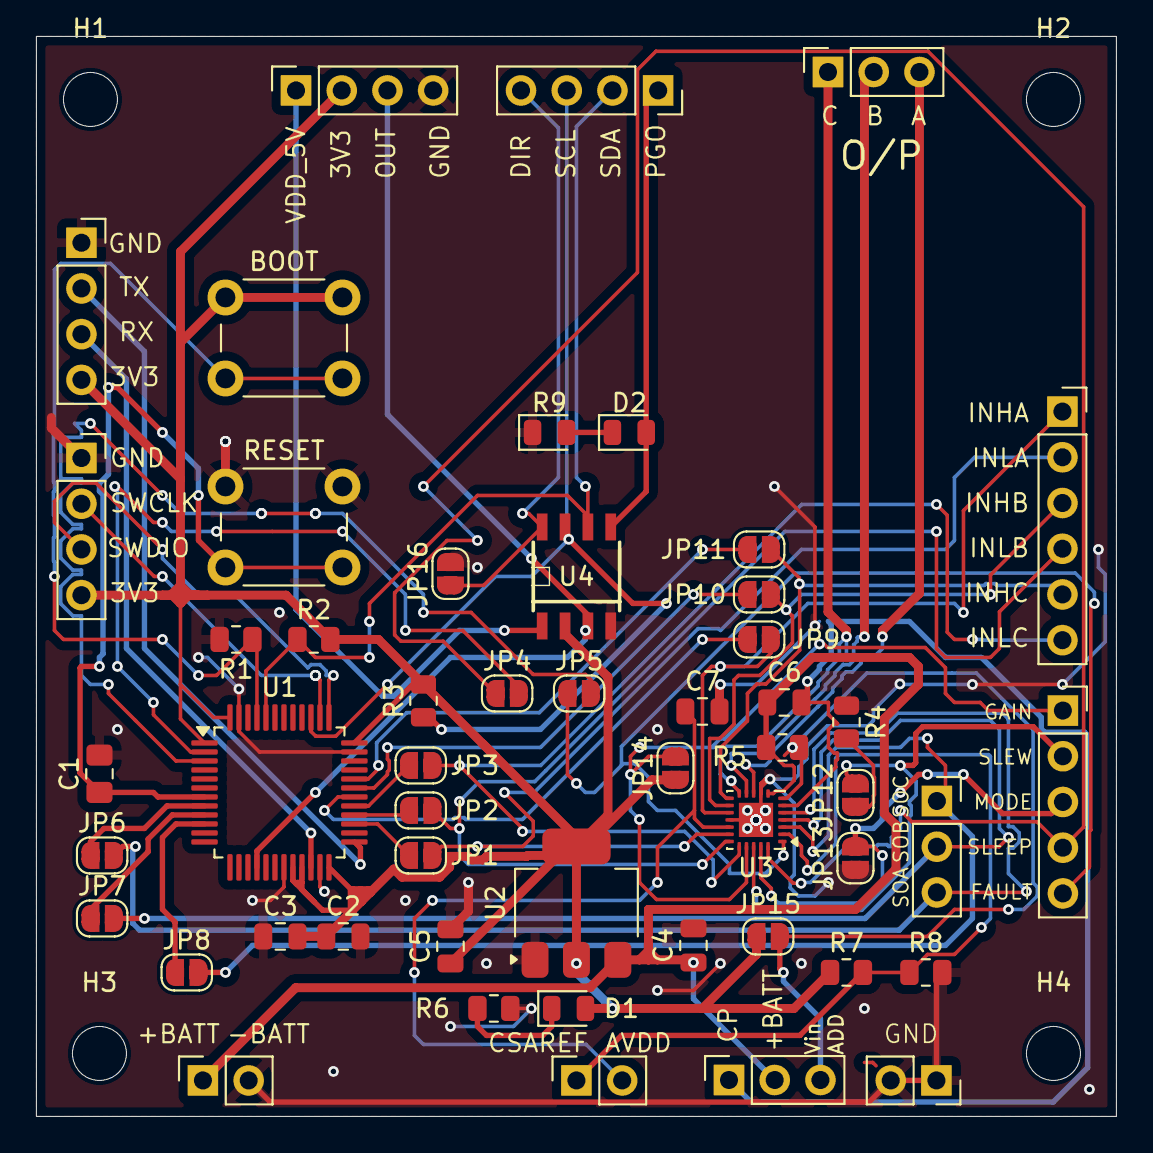
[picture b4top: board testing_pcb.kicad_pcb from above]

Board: 2 copper layers, 60.0 x 60.0 mm, 56 parts (0 on the bottom side), 50 nets.

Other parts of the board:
BOOT: SW_Push; SW_PUSH_6mm_H5mm
GND: UART; PinSocket_1x04_P2.54mm_Vertical
RESET: SW_Push; SW_PUSH_6mm_H5mm

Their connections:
+3V3: BOOT.1, GND.4; also elsewhere on the board
/BOOT: BOOT.2; also elsewhere on the board
/RESET: RESET.2; also elsewhere on the board
/RX: GND.3; also elsewhere on the board
/TX: GND.2; also elsewhere on the board
GND: GND.1, RESET.1; also elsewhere on the board

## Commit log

2026-01-29 as5600 testing script added
2026-02-04 fixed error for testing pcb
2026-02-05 minor changes
2026-02-10 made schematic look good
2026-03-26 updated versions of the 25mmX40mm daisy chaining pcb version
